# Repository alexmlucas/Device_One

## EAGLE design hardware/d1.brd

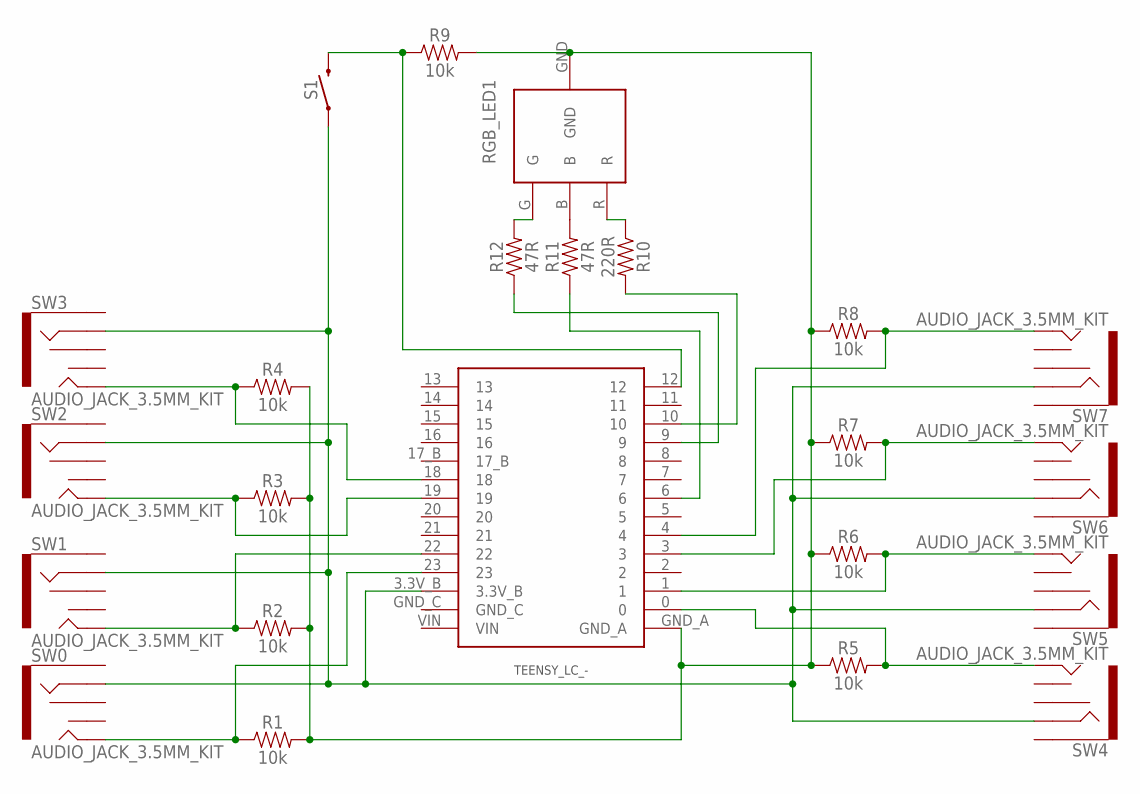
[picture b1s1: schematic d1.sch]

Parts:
R1, R2, R3, R4, R5, R6, R7, R8, R9: 10k; AXIAL-0.3-KIT
R10: 220R; AXIAL-0.3-KIT
R11, R12: 47R; AXIAL-0.3-KIT
RGB_LED1: RGB_LED_THRU; RGB_LEB_RGB_2
S1: MOMENTARY-SWITCH-SPST-PTH-6.0MM; TACTILE_SWITCH_PTH_6.0MM
SW0, SW1, SW2, SW3, SW4, SW5, SW6, SW7: AUDIO_JACK_3.5MM_KIT; AUDIO-JACK-KIT
U$1: TEENSY_LC_-

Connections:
GND: R1.P$2 (2), R2.P$2 (2), R3.P$2 (2), R4.P$2 (2), R5.P$1 (1), R6.P$1 (1), R7.P$1 (1), R8.P$1 (1), R9.P$2 (2), RGB_LED1.GND, U$1.GND_A
unnamed: R1.P$1 (1), SW0.TIP, U$1.23
unnamed: R9.P$1 (1), S1.3 (2), U$1.12
unnamed: R2.P$1 (1), SW1.TIP, U$1.22
unnamed: R3.P$1 (1), SW2.TIP, U$1.19
unnamed: R4.P$1 (1), SW3.TIP, U$1.18
unnamed: R5.P$2 (2), SW4.TIP, U$1.0
unnamed: R6.P$2 (2), SW5.TIP, U$1.1
unnamed: R7.P$2 (2), SW6.TIP, U$1.3
unnamed: R8.P$2 (2), SW7.TIP, U$1.4
unnamed: R10.P$2 (2), U$1.10
unnamed: R10.P$1 (1), RGB_LED1.R
unnamed: R12.P$1 (1), U$1.9
unnamed: R11.P$1 (1), U$1.6
unnamed: S1.1, SW0.RING, SW1.RING, SW2.RING, SW3.RING, SW4.RING, SW5.RING, SW6.RING, SW7.RING, U$1.3.3V_B
unnamed: R11.P$2 (2), RGB_LED1.B
unnamed: R12.P$2 (2), RGB_LED1.G

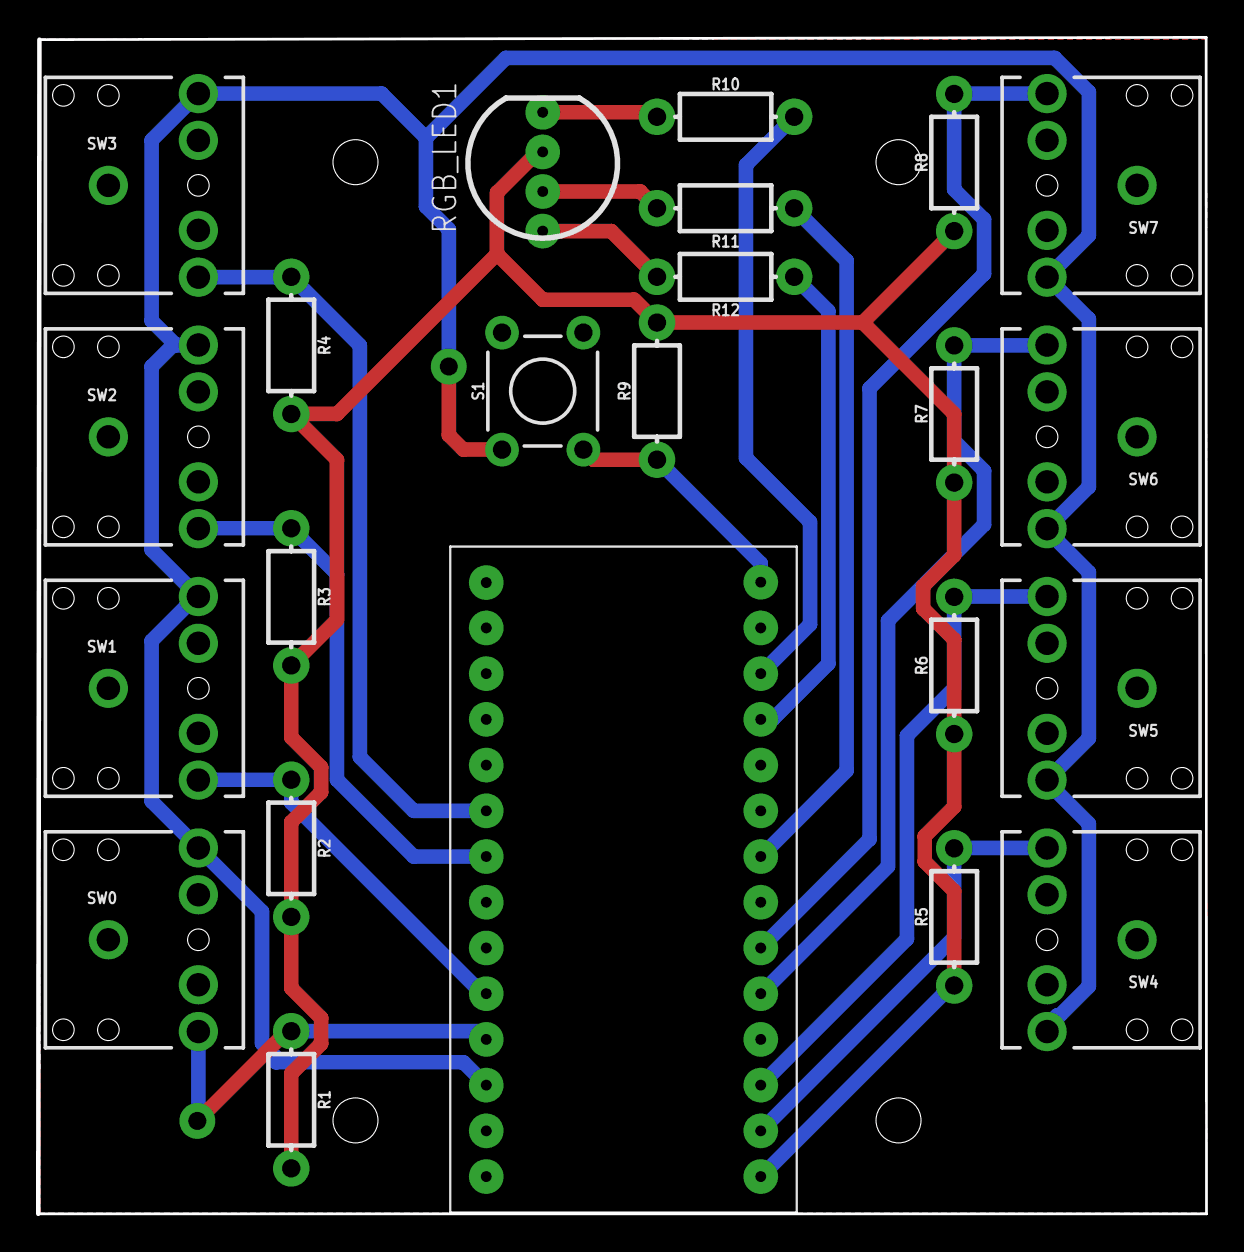
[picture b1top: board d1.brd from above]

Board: 2 copper layers, 64.8 x 65.3 mm, 23 parts (0 on the bottom side), 17 nets.

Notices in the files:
parts and their libraries:
SparkFun-Connectors: Licensing: Creative Commons ShareAlike 4.0 International - https://creativecommons.org/licenses/by-sa/4.0
